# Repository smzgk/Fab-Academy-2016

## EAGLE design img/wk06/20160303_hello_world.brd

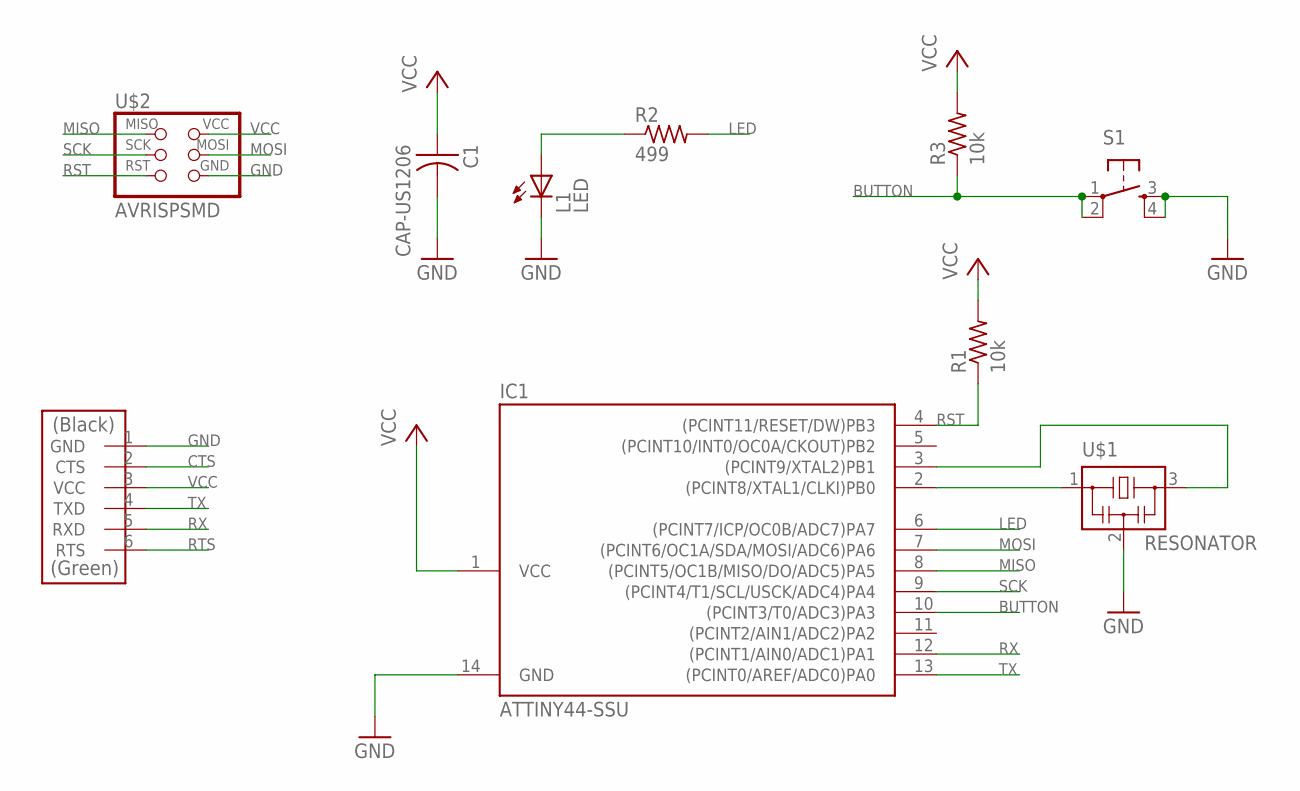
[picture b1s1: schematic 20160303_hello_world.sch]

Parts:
C1: CAP-US1206; C1206
IC1: ATTINY44-SSU; SOIC14
JP1: FTDI-SMD-HEADER; 1X06SMD
L1: LED; LED1206
R1, R3: 10k; R1206
R2: 499; R1206
S1: 6MM_SWITCH6MM_SWITCH; 6MM_SWITCH
U$1: RESONATOR; EFOBM
U$2: AVRISPSMD; 2X03SMD

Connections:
BUTTON: IC1.10 ((PCINT3/T0/ADC3)PA3), R3.1, S1.1, S1.2 (P1)
CTS: JP1.2 (CTS)
GND: C1.2, IC1.14 (GND), JP1.1 (GND), L1.2 (C), S1.3 (S), S1.4 (S1), U$1.2, U$2.6 (GND)
LED: IC1.6 ((PCINT7/ICP/OC0B/ADC7)PA7), R2.2
MISO: IC1.8 ((PCINT5/OC1B/MISO/DO/ADC5)PA5), U$2.1 (MISO)
MOSI: IC1.7 ((PCINT6/OC1A/SDA/MOSI/ADC6)PA6), U$2.4 (MOSI)
unnamed: L1.1 (A), R2.1
unnamed: IC1.2 ((PCINT8/XTAL1/CLKI)PB0), U$1.1
unnamed: IC1.3 ((PCINT9/XTAL2)PB1), U$1.3
RST: IC1.4 ((PCINT11/RESET/DW)PB3), R1.1, U$2.5 (RST)
RTS: JP1.6 (RTS)
RX: IC1.12 ((PCINT1/AIN0/ADC1)PA1), JP1.5 (RXD)
SCK: IC1.9 ((PCINT4/T1/SCL/USCK/ADC4)PA4), U$2.3 (SCK)
TX: IC1.13 ((PCINT0/AREF/ADC0)PA0), JP1.4 (TXD)
VCC: C1.1, IC1.1 (VCC), JP1.3 (VCC), R1.2, R3.2, U$2.2 (VCC)

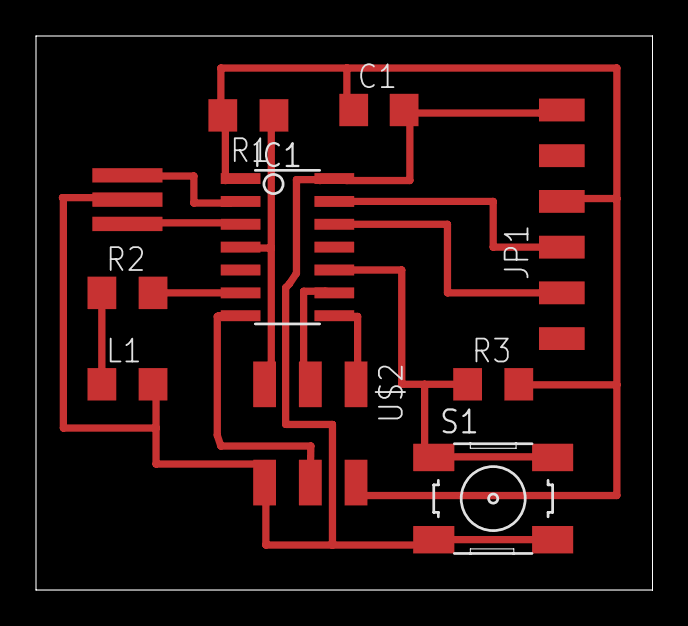
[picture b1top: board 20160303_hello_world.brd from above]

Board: 2 copper layers, 34.2 x 30.8 mm, 10 parts (0 on the bottom side), 13 nets.

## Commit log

2016-03-17 add first contents
2016-03-17 add contents of wk09 implementation for #9
2016-03-17 ad page of wk08
2016-03-22 make favicon background transparent
2016-03-22 finalize favicon
2016-03-22 resize the image of wk07
2016-03-22 resize the images of wk06
2016-03-22 resize the images of wk05
2016-03-22 resize the image of wk04
2016-03-22 resize the image of wk03
2016-03-22 resize the img of wk02
2016-03-22 resize the image of root file
2016-03-22 set origin
2016-03-22 set origin again
2016-03-22 hoge
2016-03-25 add indext to wk8
2016-03-25 modify index
2016-03-25 modify DS store file
2016-04-03 add page of wk9
2016-04-03 add contents to wk08
2016-04-03 update contents
2016-04-04 add contents of hello-echo board
2016-04-04 add vide link to page
